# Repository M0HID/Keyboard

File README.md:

# K75 - A lightweight, 75% mechanical keyboard

This is a 75% keyboard fully designed by me, including the PCB, case, and firmware. It is designed to use _KMK_, a circuitpython-based firmware for keyboards! I included a rotary encoder, as well as a few "action" keys on the side of the keyboard which can be reprogrammed to anything you want, such as media controls, text controls, or any kind of shortcut you can think of!

### The PCB:
I wanted to create a challenge for myself, and so opted to use the simple _Xiao RP2040_ as the main MCU. This is however, quite limited in terms of I/O and so i had to make use of 2 MCP23017 io expanders! I also opted to use the QFP footprint on both of them which made things slightly easier to route, given the tight space but probably going to be really hard to solder :sob:

### The BOM:
|              Item             | Part #                                                | Amount | Price [$] |
|:-----------------------------:|-------------------------------------------------------|--------|-----------|
| 0402 SMD Diodes               | C470745                                               | 82     | 0.60      |
| Akko cream yellow switches    | https://www.aliexpress.com/item/1005007665996795.html | 82     | 27.52     |
| Purple Keycap Set             | https://www.aliexpress.com/item/1005005622221680.html | 1      | 15.01     |
| Reverse Mount SK6812-Mini-E   | C5149201                                              | 86     | 5.91      |
| Xiao RP2040                   | 1597-102010428-ND                                     | 1      | 4.68      |
| MCP23017                      | C629439                                               | 2      | 3.03      |
| Mill-Max 0305 Hotswap Sockets | ED90584-ND                                            | 164    | 31.42     |
| 3D printed case shipping      |                                                       | 1      | 4.42      |
| PCB                           |                                                       |        | 26.94     |
| PCB mounted Stabilisers       | https://www.aliexpress.com/item/1005001632672798.html | 1      | 17.39     |
| Rotary Encoder                | C470745                                               | 1      | 2.81      |
| WS2812B Led Sidelighting      |                                                       | 1      | 5.53
| Total                         |                                                       |        | 139.19    |

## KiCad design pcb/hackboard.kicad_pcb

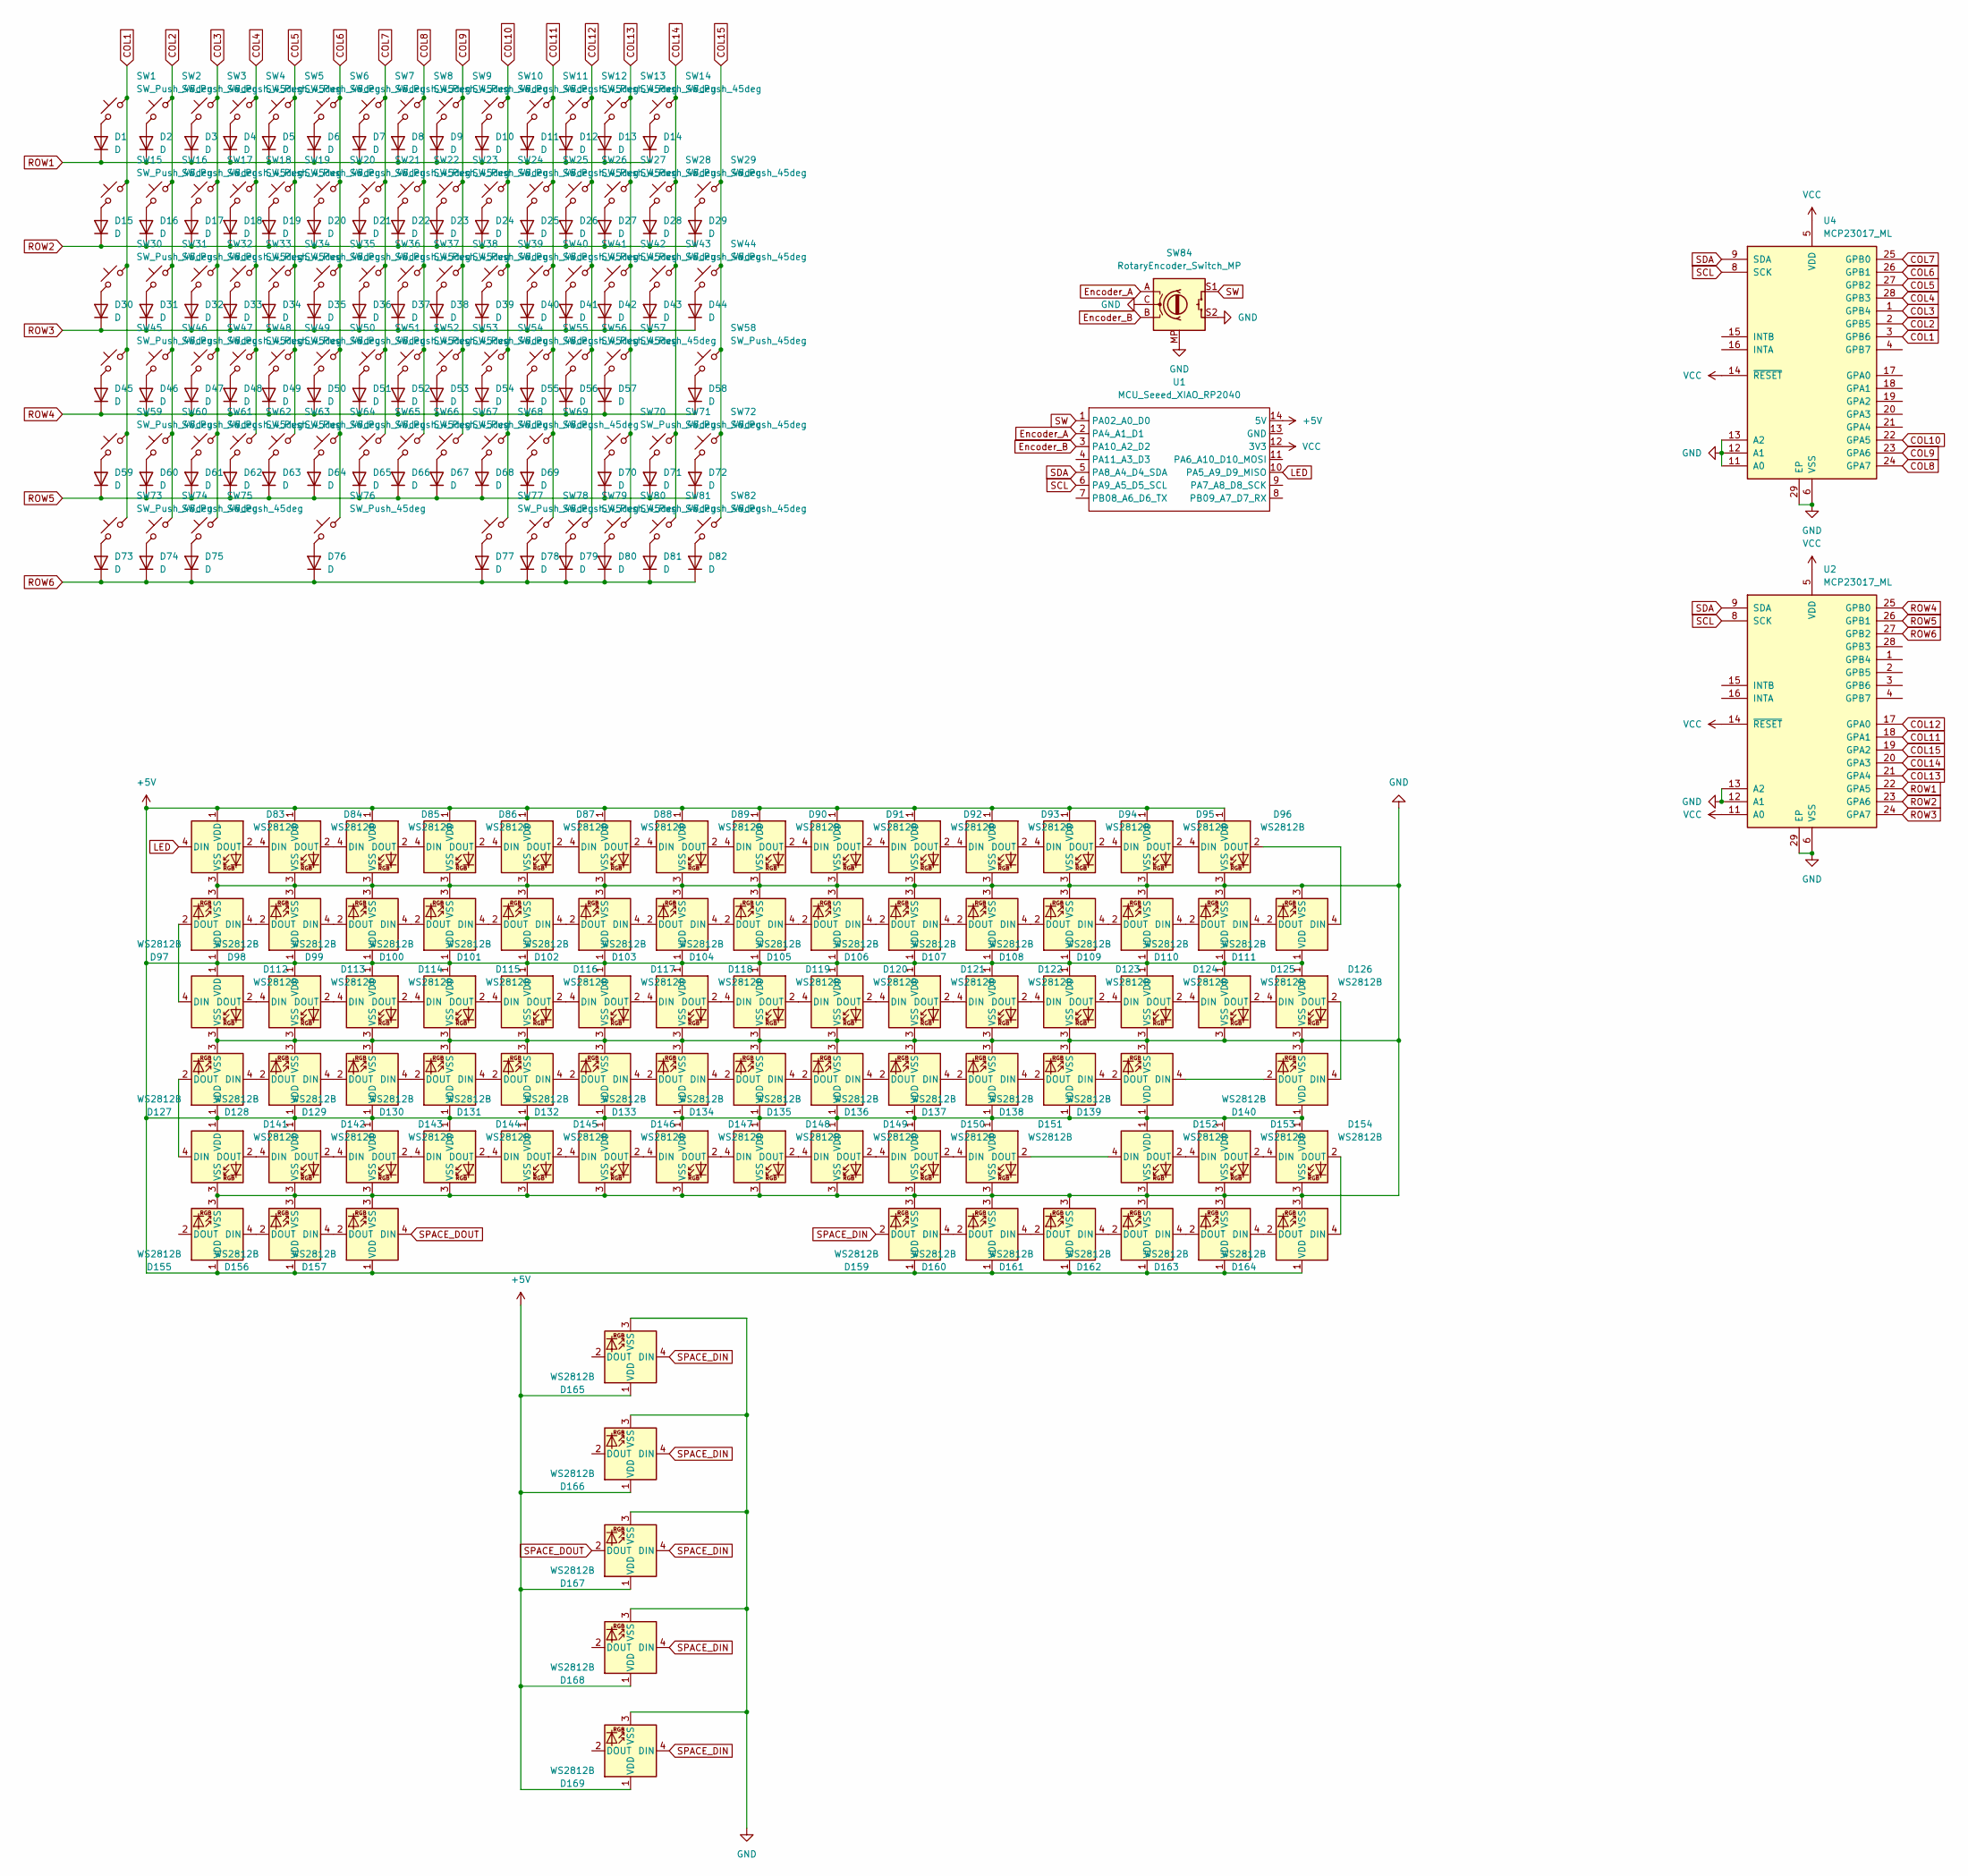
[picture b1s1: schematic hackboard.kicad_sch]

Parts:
D1, D2, D3, D4, D5, D6, D7, D8, D9, D10, D11, D12, D13, D14, D15, D16, D17, D18, D19, D20, D21, D22, D23, D24, D25, D26, D27, D28, D29, D30, D31, D32, D33, D34, D35, D36, D37, D38, D39, D40, D41, D42, D43, D44, D45, D46, D47, D48, D49, D50, D51, D52, D53, D54, D55, D56, D57, D58, D59, D60, D61, D62, D63, D64, D65, D66, D67, D68, D69, D70, D71, D72, D73, D74, D75, D76, D77, D78, D79, D80, D81, D82: D; D_SOD-123
D83, D84, D85, D86, D87, D88, D89, D90, D91, D92, D93, D94, D95, D96, D97, D98, D99, D100, D101, D102, D103, D104, D105, D106, D107, D108, D109, D110, D111, D112, D113, D114, D115, D116, D117, D118, D119, D120, D121, D122, D123, D124, D125, D126, D127, D128, D129, D130, D131, D132, D133, D134, D135, D136, D137, D138, D139, D140, D141, D142, D143, D144, D145, D146, D147, D148, D149, D150, D151, D152, D153, D154, D155, D156, D157, D159, D160, D161, D162, D163, D164, D165, D166, D167, D168, D169: WS2812B; SK6812-MINI-E
SW1, SW2, SW3, SW4, SW5, SW6, SW7, SW8, SW9, SW10, SW11, SW12, SW13, SW14, SW15, SW16, SW17, SW18, SW19, SW20, SW21, SW22, SW23, SW24, SW25, SW26, SW27, SW29, SW31, SW32, SW33, SW34, SW35, SW36, SW37, SW38, SW39, SW40, SW41, SW42, SW44, SW46, SW47, SW48, SW49, SW50, SW51, SW52, SW53, SW54, SW55, SW56, SW58, SW60, SW61, SW62, SW63, SW64, SW65, SW66, SW67, SW68, SW69, SW71, SW72, SW77, SW78, SW79, SW80, SW81, SW82: SW_Push_45deg; SW_Cherry_MX_1.00u_PCB
SW28: SW_Push_45deg; SW_Cherry_MX_2.00u_PCB
SW30, SW43: SW_Push_45deg; SW_Cherry_MX_1.50u_PCB
SW45, SW70: SW_Push_45deg; SW_Cherry_MX_1.75u_PCB
SW57, SW59: SW_Push_45deg; SW_Cherry_MX_2.25u_PCB
SW73, SW74, SW75: SW_Push_45deg; SW_Cherry_MX_1.25u_PCB
SW76: SW_Push_45deg; SW_Cherry_MX_6.25u_PCB
SW84: RotaryEncoder_Switch_MP; RotaryEncoder_Alps_EC11E-Switch_Vertical_H20mm
U1: MCU_Seeed_XIAO_RP2040; XIAO-RP2040-DIP
U2, U4: MCP23017_ML; QFN-28-1EP_6x6mm_P0.65mm_EP4.25x4.25mm

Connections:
+5V: D83.1 (VDD), D84.1 (VDD), D85.1 (VDD), D86.1 (VDD), D87.1 (VDD), D88.1 (VDD), D89.1 (VDD), D90.1 (VDD), D91.1 (VDD), D92.1 (VDD), D93.1 (VDD), D94.1 (VDD), D95.1 (VDD), D96.1 (VDD), D97.1 (VDD), D98.1 (VDD), D99.1 (VDD), D100.1 (VDD), D101.1 (VDD), D102.1 (VDD), D103.1 (VDD), D104.1 (VDD), D105.1 (VDD), D106.1 (VDD), D107.1 (VDD), D108.1 (VDD), D109.1 (VDD), D110.1 (VDD), D111.1 (VDD), D112.1 (VDD), D113.1 (VDD), D114.1 (VDD), D115.1 (VDD), D116.1 (VDD), D117.1 (VDD), D118.1 (VDD), D119.1 (VDD), D120.1 (VDD), D121.1 (VDD), D122.1 (VDD), D123.1 (VDD), D124.1 (VDD), D125.1 (VDD), D126.1 (VDD), D127.1 (VDD), D128.1 (VDD), D129.1 (VDD), D130.1 (VDD), D131.1 (VDD), D132.1 (VDD), D133.1 (VDD), D134.1 (VDD), D135.1 (VDD), D136.1 (VDD), D137.1 (VDD), D138.1 (VDD), D139.1 (VDD), D140.1 (VDD), D141.1 (VDD), D142.1 (VDD), D143.1 (VDD), D144.1 (VDD), D145.1 (VDD), D146.1 (VDD), D147.1 (VDD), D148.1 (VDD), D149.1 (VDD), D150.1 (VDD), D151.1 (VDD), D152.1 (VDD), D153.1 (VDD), D154.1 (VDD), D155.1 (VDD), D156.1 (VDD), D157.1 (VDD), D159.1 (VDD), D160.1 (VDD), D161.1 (VDD), D162.1 (VDD), D163.1 (VDD), D164.1 (VDD), D165.1 (VDD), D166.1 (VDD), D167.1 (VDD), D168.1 (VDD), D169.1 (VDD), U1.14 (5V)
COL1: SW1.2, SW15.2, SW30.2, SW45.2, SW59.2, SW73.2, U4.3 (GPB6)
COL2: SW2.2, SW16.2, SW31.2, SW46.2, SW60.2, SW74.2, U4.2 (GPB5)
COL3: SW3.2, SW17.2, SW32.2, SW47.2, SW61.2, SW75.2, U4.1 (GPB4)
COL4: SW4.2, SW18.2, SW33.2, SW48.2, SW62.2, U4.28 (GPB3)
COL5: SW5.2, SW19.2, SW34.2, SW49.2, SW63.2, U4.27 (GPB2)
COL6: SW6.2, SW20.2, SW35.2, SW50.2, SW64.2, SW76.2, U4.26 (GPB1)
COL7: SW7.2, SW21.2, SW36.2, SW51.2, SW65.2, U4.25 (GPB0)
COL8: SW8.2, SW22.2, SW37.2, SW52.2, SW66.2, U4.24 (GPA7)
COL9: SW9.2, SW23.2, SW38.2, SW53.2, SW67.2, U4.23 (GPA6)
COL10: SW10.2, SW24.2, SW39.2, SW54.2, SW68.2, SW77.2, U4.22 (GPA5)
COL11: SW11.2, SW25.2, SW40.2, SW55.2, SW69.2, SW78.2, U2.18 (GPA1)
COL12: SW12.2, SW26.2, SW41.2, SW56.2, SW79.2, U2.17 (GPA0)
COL13: SW13.2, SW27.2, SW42.2, SW57.2, SW70.2, SW80.2, U2.21 (GPA4)
COL14: SW14.2, SW28.2, SW43.2, SW71.2, SW81.2, U2.20 (GPA3)
COL15: SW29.2, SW44.2, SW58.2, SW72.2, SW82.2, U2.19 (GPA2)
Encoder_A: SW84.A, U1.2 (PA4_A1_D1)
Encoder_B: SW84.B, U1.3 (PA10_A2_D2)
GND: D83.3 (VSS), D84.3 (VSS), D85.3 (VSS), D86.3 (VSS), D87.3 (VSS), D88.3 (VSS), D89.3 (VSS), D90.3 (VSS), D91.3 (VSS), D92.3 (VSS), D93.3 (VSS), D94.3 (VSS), D95.3 (VSS), D96.3 (VSS), D97.3 (VSS), D98.3 (VSS), D99.3 (VSS), D100.3 (VSS), D101.3 (VSS), D102.3 (VSS), D103.3 (VSS), D104.3 (VSS), D105.3 (VSS), D106.3 (VSS), D107.3 (VSS), D108.3 (VSS), D109.3 (VSS), D110.3 (VSS), D111.3 (VSS), D112.3 (VSS), D113.3 (VSS), D114.3 (VSS), D115.3 (VSS), D116.3 (VSS), D117.3 (VSS), D118.3 (VSS), D119.3 (VSS), D120.3 (VSS), D121.3 (VSS), D122.3 (VSS), D123.3 (VSS), D124.3 (VSS), D125.3 (VSS), D126.3 (VSS), D127.3 (VSS), D128.3 (VSS), D129.3 (VSS), D130.3 (VSS), D131.3 (VSS), D132.3 (VSS), D133.3 (VSS), D134.3 (VSS), D135.3 (VSS), D136.3 (VSS), D137.3 (VSS), D138.3 (VSS), D139.3 (VSS), D140.3 (VSS), D141.3 (VSS), D142.3 (VSS), D143.3 (VSS), D144.3 (VSS), D145.3 (VSS), D146.3 (VSS), D147.3 (VSS), D148.3 (VSS), D149.3 (VSS), D150.3 (VSS), D151.3 (VSS), D152.3 (VSS), D153.3 (VSS), D154.3 (VSS), D155.3 (VSS), D156.3 (VSS), D157.3 (VSS), D159.3 (VSS), D160.3 (VSS), D161.3 (VSS), D162.3 (VSS), D163.3 (VSS), D164.3 (VSS), D165.3 (VSS), D166.3 (VSS), D167.3 (VSS), D168.3 (VSS), D169.3 (VSS), SW84.C, SW84.MP, SW84.S2, U2.6 (VSS), U2.12 (A1), U2.13 (A2), U2.29 (EP), U4.6 (VSS), U4.11 (A0), U4.12 (A1), U4.13 (A2), U4.29 (EP)
LED: D83.4 (DIN), U1.10 (PA5_A9_D9_MISO)
unnamed: D1.2 (A), SW1.1
unnamed: D2.2 (A), SW2.1
unnamed: D3.2 (A), SW3.1
unnamed: D4.2 (A), SW4.1
unnamed: D5.2 (A), SW5.1
unnamed: D6.2 (A), SW6.1
unnamed: D7.2 (A), SW7.1
unnamed: D8.2 (A), SW8.1
unnamed: D9.2 (A), SW9.1
unnamed: D10.2 (A), SW10.1
unnamed: D11.2 (A), SW11.1
unnamed: D12.2 (A), SW12.1
unnamed: D13.2 (A), SW13.1
unnamed: D14.2 (A), SW14.1
unnamed: D15.2 (A), SW15.1
unnamed: D16.2 (A), SW16.1
unnamed: D17.2 (A), SW17.1
unnamed: D18.2 (A), SW18.1
unnamed: D19.2 (A), SW19.1
unnamed: D20.2 (A), SW20.1
unnamed: D21.2 (A), SW21.1
unnamed: D22.2 (A), SW22.1
unnamed: D23.2 (A), SW23.1
unnamed: D24.2 (A), SW24.1
unnamed: D25.2 (A), SW25.1
unnamed: D26.2 (A), SW26.1
unnamed: D27.2 (A), SW27.1
unnamed: D28.2 (A), SW28.1
unnamed: D29.2 (A), SW29.1
unnamed: D30.2 (A), SW30.1
unnamed: D31.2 (A), SW31.1
unnamed: D32.2 (A), SW32.1
unnamed: D33.2 (A), SW33.1
unnamed: D34.2 (A), SW34.1
unnamed: D35.2 (A), SW35.1
unnamed: D36.2 (A), SW36.1
unnamed: D37.2 (A), SW37.1
unnamed: D38.2 (A), SW38.1
unnamed: D39.2 (A), SW39.1
unnamed: D40.2 (A), SW40.1
unnamed: D41.2 (A), SW41.1
unnamed: D42.2 (A), SW42.1
unnamed: D43.2 (A), SW43.1
unnamed: D44.2 (A), SW44.1
unnamed: D45.2 (A), SW45.1
unnamed: D46.2 (A), SW46.1
unnamed: D47.2 (A), SW47.1
unnamed: D48.2 (A), SW48.1
unnamed: D49.2 (A), SW49.1
unnamed: D50.2 (A), SW50.1
unnamed: D51.2 (A), SW51.1
unnamed: D52.2 (A), SW52.1
unnamed: D53.2 (A), SW53.1
unnamed: D54.2 (A), SW54.1
unnamed: D55.2 (A), SW55.1
unnamed: D56.2 (A), SW56.1
unnamed: D57.2 (A), SW57.1
unnamed: D58.2 (A), SW58.1
unnamed: D59.2 (A), SW59.1
unnamed: D60.2 (A), SW60.1
unnamed: D61.2 (A), SW61.1
unnamed: D62.2 (A), SW62.1
unnamed: D63.2 (A), SW63.1
unnamed: D64.2 (A), SW64.1
unnamed: D65.2 (A), SW65.1
unnamed: D66.2 (A), SW66.1
unnamed: D67.2 (A), SW67.1
unnamed: D68.2 (A), SW68.1
unnamed: D69.2 (A), SW69.1
unnamed: D70.2 (A), SW70.1
unnamed: D71.2 (A), SW71.1
unnamed: D72.2 (A), SW72.1
unnamed: D73.2 (A), SW73.1
unnamed: D74.2 (A), SW74.1
unnamed: D75.2 (A), SW75.1
unnamed: D76.2 (A), SW76.1
unnamed: D77.2 (A), SW77.1
unnamed: D78.2 (A), SW78.1
unnamed: D79.2 (A), SW79.1
unnamed: D80.2 (A), SW80.1
unnamed: D81.2 (A), SW81.1
unnamed: D82.2 (A), SW82.1
unnamed: D83.2 (DOUT), D84.4 (DIN)
unnamed: D84.2 (DOUT), D85.4 (DIN)
unnamed: D85.2 (DOUT), D86.4 (DIN)
unnamed: D86.2 (DOUT), D87.4 (DIN)
unnamed: D87.2 (DOUT), D88.4 (DIN)
unnamed: D88.2 (DOUT), D89.4 (DIN)
unnamed: D89.2 (DOUT), D90.4 (DIN)
unnamed: D90.2 (DOUT), D91.4 (DIN)
unnamed: D91.2 (DOUT), D92.4 (DIN)
unnamed: D92.2 (DOUT), D93.4 (DIN)
unnamed: D93.2 (DOUT), D94.4 (DIN)
unnamed: D94.2 (DOUT), D95.4 (DIN)
unnamed: D95.2 (DOUT), D96.4 (DIN)
unnamed: D97.4 (DIN), D98.2 (DOUT)
unnamed: D98.4 (DIN), D99.2 (DOUT)
unnamed: D100.4 (DIN), D101.2 (DOUT)
unnamed: D99.4 (DIN), D100.2 (DOUT)
unnamed: D101.4 (DIN), D102.2 (DOUT)
unnamed: D102.4 (DIN), D103.2 (DOUT)
unnamed: D103.4 (DIN), D104.2 (DOUT)
unnamed: D104.4 (DIN), D105.2 (DOUT)
unnamed: D105.4 (DIN), D106.2 (DOUT)
unnamed: D106.4 (DIN), D107.2 (DOUT)
unnamed: D107.4 (DIN), D108.2 (DOUT)
unnamed: D108.4 (DIN), D109.2 (DOUT)
unnamed: D109.4 (DIN), D110.2 (DOUT)
unnamed: D110.4 (DIN), D111.2 (DOUT)
unnamed: D96.2 (DOUT), D111.4 (DIN)
unnamed: D97.2 (DOUT), D112.4 (DIN)
unnamed: D112.2 (DOUT), D113.4 (DIN)
unnamed: D113.2 (DOUT), D114.4 (DIN)
unnamed: D114.2 (DOUT), D115.4 (DIN)
unnamed: D115.2 (DOUT), D116.4 (DIN)
unnamed: D116.2 (DOUT), D117.4 (DIN)
unnamed: D117.2 (DOUT), D118.4 (DIN)
unnamed: D118.2 (DOUT), D119.4 (DIN)
unnamed: D119.2 (DOUT), D120.4 (DIN)
unnamed: D120.2 (DOUT), D121.4 (DIN)
unnamed: D121.2 (DOUT), D122.4 (DIN)
unnamed: D122.2 (DOUT), D123.4 (DIN)
unnamed: D123.2 (DOUT), D124.4 (DIN)
unnamed: D124.2 (DOUT), D125.4 (DIN)
unnamed: D125.2 (DOUT), D126.4 (DIN)
unnamed: D126.2 (DOUT), D140.4 (DIN)
unnamed: D127.4 (DIN), D128.2 (DOUT)
unnamed: D127.2 (DOUT), D141.4 (DIN)
unnamed: D128.4 (DIN), D129.2 (DOUT)
unnamed: D129.4 (DIN), D130.2 (DOUT)
unnamed: D130.4 (DIN), D131.2 (DOUT)
unnamed: D131.4 (DIN), D132.2 (DOUT)
unnamed: D132.4 (DIN), D133.2 (DOUT)
unnamed: D133.4 (DIN), D134.2 (DOUT)
unnamed: D134.4 (DIN), D135.2 (DOUT)
unnamed: D135.4 (DIN), D136.2 (DOUT)
unnamed: D136.4 (DIN), D137.2 (DOUT)
unnamed: D137.4 (DIN), D138.2 (DOUT)
unnamed: D138.4 (DIN), D139.2 (DOUT)
unnamed: D139.4 (DIN), D140.2 (DOUT)
unnamed: D141.2 (DOUT), D142.4 (DIN)
unnamed: D142.2 (DOUT), D143.4 (DIN)
unnamed: D143.2 (DOUT), D144.4 (DIN)
unnamed: D144.2 (DOUT), D145.4 (DIN)
unnamed: D145.2 (DOUT), D146.4 (DIN)
unnamed: D146.2 (DOUT), D147.4 (DIN)
unnamed: D147.2 (DOUT), D148.4 (DIN)
unnamed: D148.2 (DOUT), D149.4 (DIN)
unnamed: D149.2 (DOUT), D150.4 (DIN)
unnamed: D150.2 (DOUT), D151.4 (DIN)
unnamed: D151.2 (DOUT), D152.4 (DIN)
unnamed: D152.2 (DOUT), D153.4 (DIN)
unnamed: D153.2 (DOUT), D154.4 (DIN)
unnamed: D154.2 (DOUT), D164.4 (DIN)
unnamed: D155.4 (DIN), D156.2 (DOUT)
unnamed: D156.4 (DIN), D157.2 (DOUT)
unnamed: D159.4 (DIN), D160.2 (DOUT)
unnamed: D160.4 (DIN), D161.2 (DOUT)
unnamed: D161.4 (DIN), D162.2 (DOUT)
unnamed: D162.4 (DIN), D163.2 (DOUT)
unnamed: D163.4 (DIN), D164.2 (DOUT)
ROW1: D1.1 (K), D2.1 (K), D3.1 (K), D4.1 (K), D5.1 (K), D6.1 (K), D7.1 (K), D8.1 (K), D9.1 (K), D10.1 (K), D11.1 (K), D12.1 (K), D13.1 (K), D14.1 (K), U2.22 (GPA5)
ROW2: D15.1 (K), D16.1 (K), D17.1 (K), D18.1 (K), D19.1 (K), D20.1 (K), D21.1 (K), D22.1 (K), D23.1 (K), D24.1 (K), D25.1 (K), D26.1 (K), D27.1 (K), D28.1 (K), D29.1 (K), U2.23 (GPA6)
ROW3: D30.1 (K), D31.1 (K), D32.1 (K), D33.1 (K), D34.1 (K), D35.1 (K), D36.1 (K), D37.1 (K), D38.1 (K), D39.1 (K), D40.1 (K), D41.1 (K), D42.1 (K), D43.1 (K), D44.1 (K), U2.24 (GPA7)
ROW4: D45.1 (K), D46.1 (K), D47.1 (K), D48.1 (K), D49.1 (K), D50.1 (K), D51.1 (K), D52.1 (K), D53.1 (K), D54.1 (K), D55.1 (K), D56.1 (K), D57.1 (K), D58.1 (K), U2.25 (GPB0)
ROW5: D59.1 (K), D60.1 (K), D61.1 (K), D62.1 (K), D63.1 (K), D64.1 (K), D65.1 (K), D66.1 (K), D67.1 (K), D68.1 (K), D69.1 (K), D70.1 (K), D71.1 (K), D72.1 (K), U2.26 (GPB1)
ROW6: D73.1 (K), D74.1 (K), D75.1 (K), D76.1 (K), D77.1 (K), D78.1 (K), D79.1 (K), D80.1 (K), D81.1 (K), D82.1 (K), U2.27 (GPB2)
SCL: U1.6 (PA9_A5_D5_SCL), U2.8 (SCK), U4.8 (SCK)
SDA: U1.5 (PA8_A4_D4_SDA), U2.9 (SDA), U4.9 (SDA)
SPACE_DIN: D159.2 (DOUT), D165.4 (DIN), D166.4 (DIN), D167.4 (DIN), D168.4 (DIN), D169.4 (DIN)
SPACE_DOUT: D157.4 (DIN), D167.2 (DOUT)
SW: SW84.S1, U1.1 (PA02_A0_D0)
VCC: U1.12 (3V3), U2.5 (VDD), U2.11 (A0), U2.14 (~RESET), U4.5 (VDD), U4.14 (~RESET)

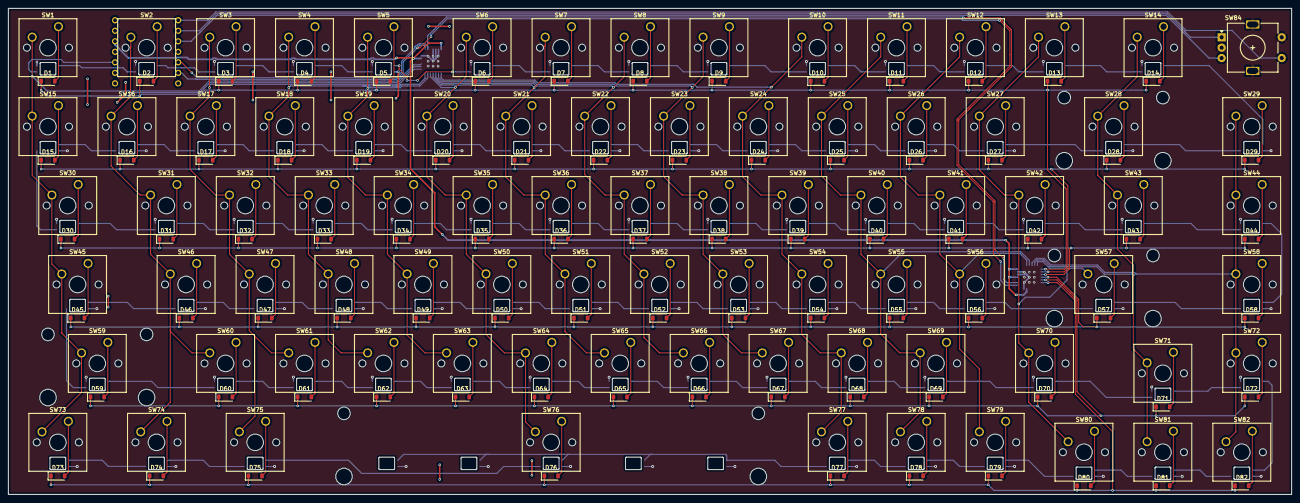
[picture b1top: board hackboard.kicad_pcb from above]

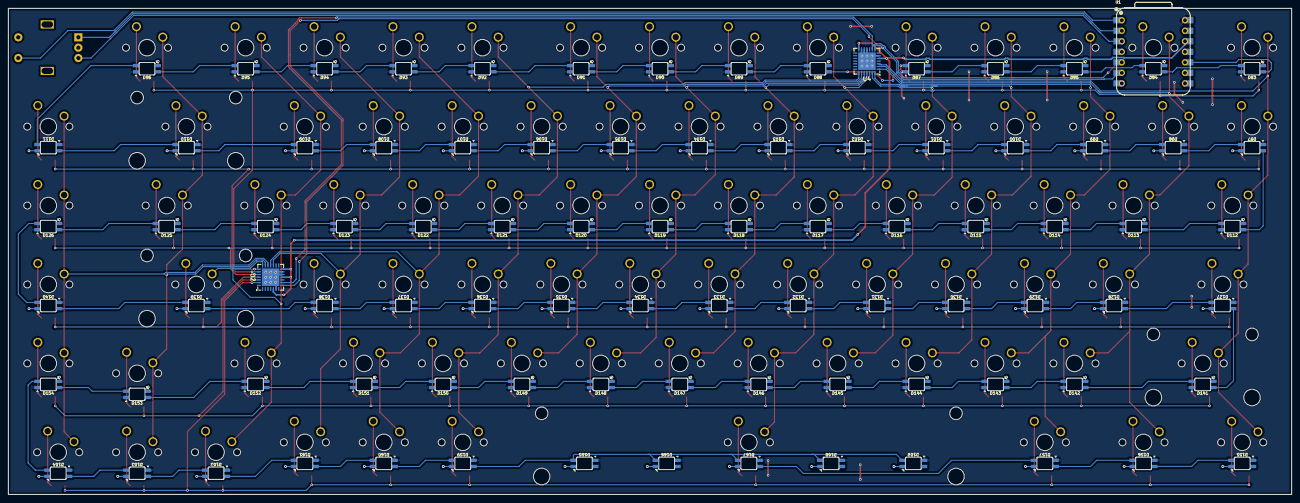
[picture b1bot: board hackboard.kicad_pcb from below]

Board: 2 copper layers, 309.7 x 117.3 mm, 254 parts (89 on the bottom side), 193 nets.

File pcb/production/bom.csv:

Designator,Footprint,Quantity,Value,LCSC Part #
"D1, D10, D11, D12, D13, D14, D15, D16, D17, D18, D19, D2, D20, D21, D22, D23, D24, D25, D26, D27, D28, D29, D3, D30, D31, D32, D33, D34, D35, D36, D37, D38, D39, D4, D40, D41, D42, D43, D44, D45, D46, D47, D48, D49, D5, D50, D51, D52, D53, D54, D55, D56, D57, D58, D59, D6, D60, D61, D62, D63, D64, D65, D66, D67, D68, D69, D7, D70, D71, D72, D73, D74, D75, D76, D77, D78, D79, D8, D80, D81, D82, D9",D_SOD-123,82,D,
"D100, D101, D102, D103, D104, D105, D106, D107, D108, D109, D110, D111, D112, D113, D114, D115, D116, D117, D118, D119, D120, D121, D122, D123, D124, D125, D126, D127, D128, D129, D130, D131, D132, D133, D134, D135, D136, D137, D138, D139, D140, D141, D142, D143, D144, D145, D146, D147, D148, D149, D150, D151, D152, D153, D154, D155, D156, D157, D159, D160, D161, D162, D163, D164, D165, D166, D167, D168, D169, D83, D84, D85, D86, D87, D88, D89, D90, D91, D92, D93, D94, D95, D96, D97, D98, D99",SK6812-MINI-E,86,WS2812B,
"SW1, SW10, SW11, SW12, SW13, SW14, SW15, SW16, SW17, SW18, SW19, SW2, SW20, SW21, SW22, SW23, SW24, SW25, SW26, SW27, SW29, SW3, SW31, SW32, SW33, SW34, SW35, SW36, SW37, SW38, SW39, SW4, SW40, SW41, SW42, SW44, SW46, SW47, SW48, SW49, SW5, SW50, SW51, SW52, SW53, SW54, SW55, SW56, SW58, SW6, SW60, SW61, SW62, SW63, SW64, SW65, SW66, SW67, SW68, SW69, SW7, SW71, SW72, SW77, SW78, SW79, SW8, SW80, SW81, SW82, SW9",SW_Cherry_MX_1.00u_PCB,71,SW_Push_45deg,
SW28,SW_Cherry_MX_2.00u_PCB,1,SW_Push_45deg,
"SW30, SW43",SW_Cherry_MX_1.50u_PCB,2,SW_Push_45deg,
"SW45, SW70",SW_Cherry_MX_1.75u_PCB,2,SW_Push_45deg,
"SW57, SW59",SW_Cherry_MX_2.25u_PCB,2,SW_Push_45deg,
"SW73, SW74, SW75",SW_Cherry_MX_1.25u_PCB,3,SW_Push_45deg,
SW76,SW_Cherry_MX_6.25u_PCB,1,SW_Push_45deg,
SW84,RotaryEncoder_Alps_EC11E-Switch_Vertical_H20mm,1,RotaryEncoder_Switch_MP,
U1,XIAO-RP2040-DIP,1,MCU_Seeed_XIAO_RP2040,
"U2, U4",QFN-28-1EP_6x6mm_P0.65mm_EP4.25x4.25mm,2,MCP23017_ML,

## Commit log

2025-07-31 add pcb files
2025-07-31 add fw
2025-07-31 add total
2025-07-31 folders
2025-08-09 add total time
2025-08-21 update files
2025-08-21 update pcb
2025-08-21 modified: pcb/hackboard.kicad_pcb modified: pcb/hackboard.kicad_prl modified: pcb/hackboard.kicad_sch modified: pcb/production/bom.csv modified: pcb/production/hackboard.zip modified: pcb/production/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
